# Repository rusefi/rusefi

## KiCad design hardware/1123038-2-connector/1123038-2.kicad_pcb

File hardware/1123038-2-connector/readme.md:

72 pin connector Mazda Miata MX-5 NB2

# [For sale here](https://www.tindie.com/products/russian/72p-connector-bare-pcb-miata-nb2/)

[Known Issues](known_issues.txt)

[Forum thread](https://rusefi.com/forum/viewtopic.php?f=4&t=687)

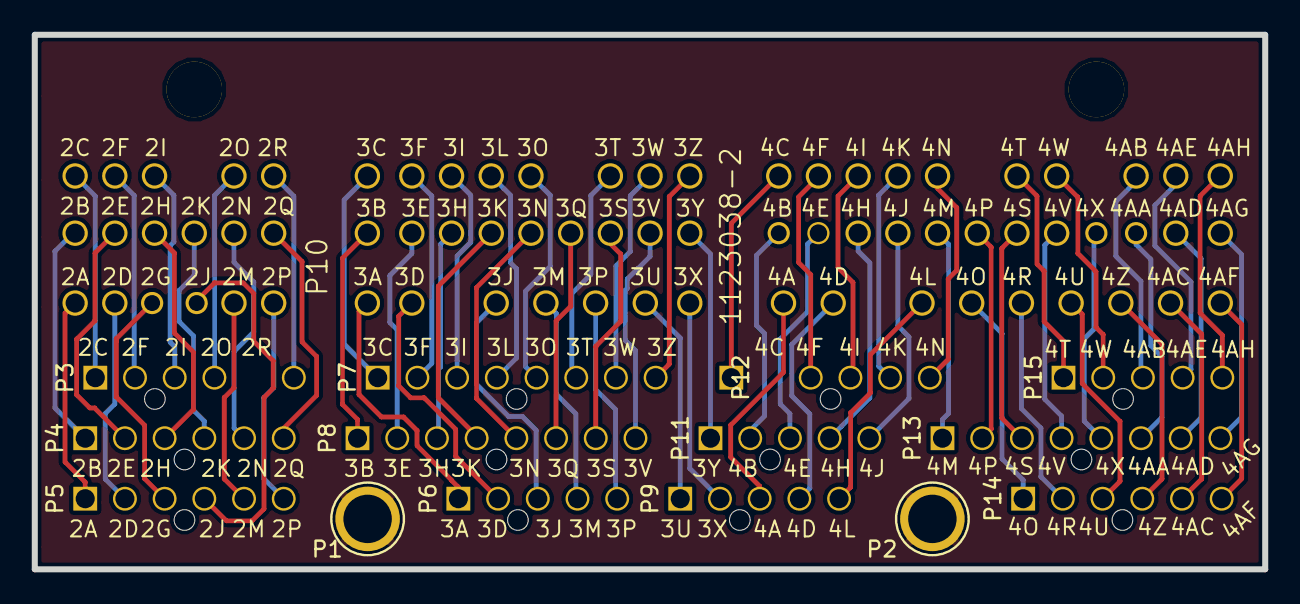
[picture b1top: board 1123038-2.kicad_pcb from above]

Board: 2 copper layers, 77.5 x 33.7 mm, 16 parts (1 on the bottom side), 73 nets.

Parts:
G1: LOGO
P1, P2: CONN_1; 1pin
P3, P6, P9, P11, P12, P15: CONN_01X05; Molex_NanoFit_1x05x2.50mm_Straight
P4, P5, P14: CONN_01X06; Molex_NanoFit_1x06x2.50mm_Straight
P7, P8, P13: CONN_01X08; Molex_NanoFit_1x08x2.50mm_Straight
P10: 1123038-2

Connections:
/2A: P5.1, P10.51
/2B: P4.1, P10.24
/2C: P3.1, P10.1
/2D: P5.2, P10.52
/2E: P4.2, P10.25
/2F: P3.2, P10.2
/2G: P5.3, P10.53
/2H: P4.3, P10.26
/2I: P3.3, P10.3
/2J: P5.4, P10.54
/2K: P4.4, P10.27
/2M: P5.5, P10.55
/2N: P4.5, P10.28
/2P: P5.6, P10.56
/2Q: P4.6, P10.29
/2R: P3.5, P10.5
/3A: P6.1, P10.57
/3B: P8.1, P10.30
/3C: P7.1, P10.6
/3D: P6.2, P10.58
/3E: P8.2, P10.31
/3F: P7.2, P10.7
/3H: P8.3, P10.32
/3I: P7.3, P10.8
/3J: P6.3, P10.59
/3K: P8.4, P10.33
/3L: P7.4, P10.9
/3M: P6.4, P10.60
/3N: P8.5, P10.34
/3O: P7.5, P10.10
/3P: P6.5, P10.61
/3Q: P8.6, P10.35
/3S: P8.7, P10.36
/3T: P7.6, P10.11
/3U: P9.1, P10.62
/3V: P8.8, P10.37
/3W: P7.7, P10.12
/3X: P9.2, P10.63
/3Y: P10.38, P11.1
/3Z: P7.8, P10.13
/4A: P9.3, P10.64
/4AA: P10.48, P13.6
/4AB: P10.21, P15.3
/4AC: P10.71, P14.5
/4AD: P10.49, P13.7
/4AE: P10.22, P15.4
/4AF: P10.72, P14.6
/4AG: P10.50, P13.8
/4AH: P10.23, P15.5
/4B: P10.39, P11.2
/4C: P10.14, P12.1
/4D: P9.4, P10.65
/4E: P10.40, P11.3
/4F: P10.15, P12.2
/4H: P10.41, P11.4
/4I: P10.16, P12.3
/4J: P10.42, P11.5
/4K: P10.17, P12.4
/4L: P9.5, P10.66
/4M: P10.43, P13.1
/4N: P10.18, P12.5
/4O: P10.67, P14.1
/4P: P10.44, P13.2
/4R: P10.68, P14.2
/4S: P10.45, P13.3
/4T: P10.19, P15.1
/4U: P10.69, P14.3
/4V: P10.46, P13.4
/4W: P10.20, P15.2
/4X: P10.47, P13.5
/4Z: P10.70, P14.4
/20: P3.4, P10.4
GND: P1.1, P2.1

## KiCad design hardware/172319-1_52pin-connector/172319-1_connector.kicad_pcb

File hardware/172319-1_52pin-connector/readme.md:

52 pin connector Mitsubishi Galant VR4 Eclipse 1G

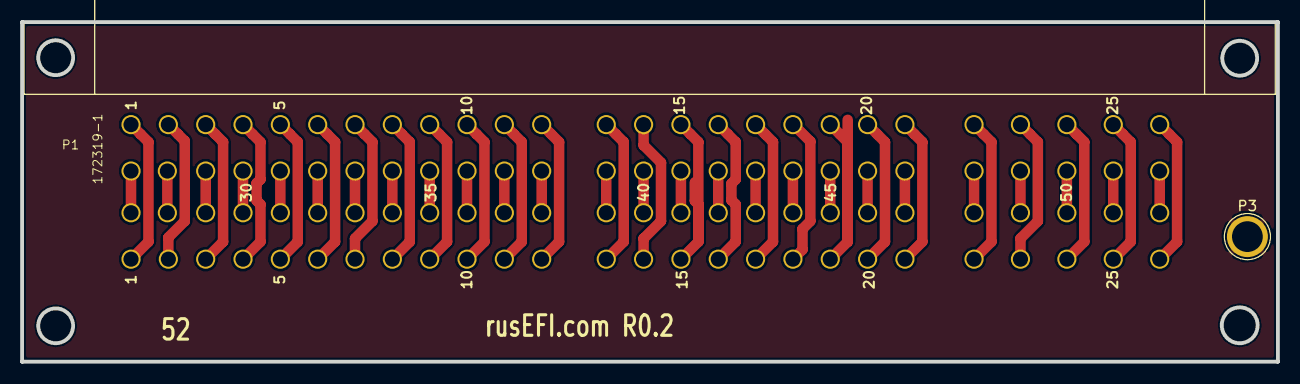
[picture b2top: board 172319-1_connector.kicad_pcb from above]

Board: 2 copper layers, 124.5 x 33.7 mm, 3 parts (1 on the bottom side), 52 nets.

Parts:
P1, P2: 172319-1; 172319-1_connector
P3: CONN_01X01; 1pin

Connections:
unnamed: P1.1, P2.1
unnamed: P1.2, P2.2
unnamed: P1.3, P2.3
unnamed: P1.4, P2.4
unnamed: P1.5, P2.5
unnamed: P1.6, P2.6
unnamed: P1.7, P2.7
unnamed: P1.8, P2.8
unnamed: P1.9, P2.9
unnamed: P1.10, P2.10
unnamed: P1.11, P2.11
unnamed: P1.12, P2.12
unnamed: P1.13, P2.13
unnamed: P1.14, P2.14
unnamed: P1.15, P2.15
unnamed: P1.16, P2.16
unnamed: P1.17, P2.17
unnamed: P1.18, P2.18
unnamed: P1.19, P2.19
unnamed: P1.20, P2.20
unnamed: P1.21, P2.21
unnamed: P1.22, P2.22
unnamed: P1.23, P2.23
unnamed: P1.24, P2.24
unnamed: P1.25, P2.25
unnamed: P1.26, P2.26
unnamed: P1.27, P2.27
unnamed: P1.28, P2.28
unnamed: P1.29, P2.29
unnamed: P1.30, P2.30
unnamed: P1.31, P2.31
unnamed: P1.32, P2.32
unnamed: P1.33, P2.33
unnamed: P1.34, P2.34
unnamed: P1.35, P2.35
unnamed: P1.36, P2.36
unnamed: P1.37, P2.37
unnamed: P1.38, P2.38
unnamed: P1.39, P2.39
unnamed: P1.40, P2.40
unnamed: P1.41, P2.41
unnamed: P1.42, P2.42
unnamed: P1.43, P2.43
unnamed: P1.44, P2.44
unnamed: P1.45, P2.45
unnamed: P1.46, P2.46
unnamed: P1.47, P2.47
unnamed: P1.48, P2.48
unnamed: P1.49, P2.49
unnamed: P1.50, P2.50
unnamed: P1.51, P2.51
unnamed: P1.52, P2.52

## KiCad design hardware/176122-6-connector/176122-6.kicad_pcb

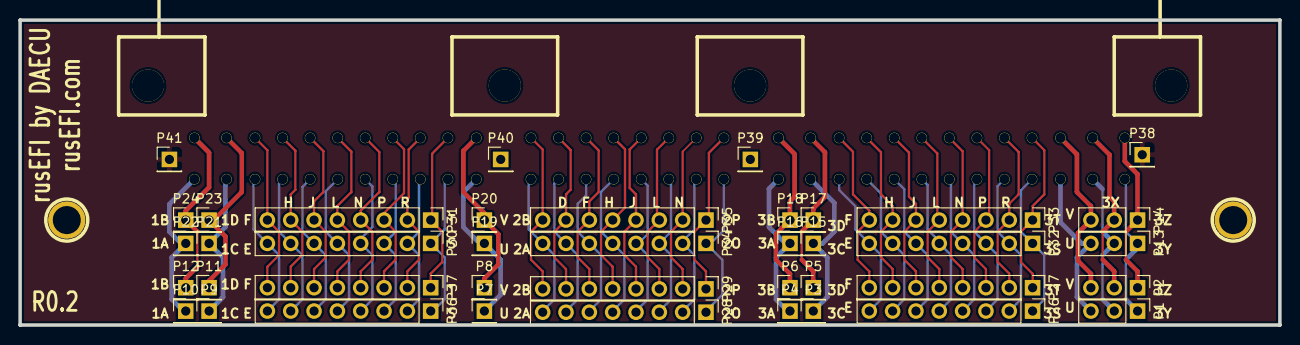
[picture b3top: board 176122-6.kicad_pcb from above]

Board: 2 copper layers, 137.2 x 33.2 mm, 43 parts (0 on the bottom side), 65 nets.

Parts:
1PIN, 1PIN#2: P***; 1pin
P1, P2, P13, P14: CONN_3; PinHeader_1x03_P2.54mm_Vertical
P3, P4, P5, P6, P7, P8, P9, P10, P11, P12, P15, P16, P17, P18, P19, P20, P21, P22, P23, P24, P38, P39, P40, P41: CONN_1; PinHeader_1x01_P2.54mm_Vertical
P25: 0176122-06; 176122-6
P26, P27, P28, P29, P30, P31, P32, P33, P34, P35, P36, P37: CONN_8; PinHeader_1x08_P2.54mm_Vertical

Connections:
GND: P38.1, P41.1
unnamed: P1.1, P13.1, P25.1
unnamed: P1.2, P13.2, P25.2
unnamed: P1.3, P13.3, P25.3
unnamed: P10.1, P22.1, P25.14
unnamed: P11.1, P23.1, P25.15
unnamed: P12.1, P24.1, P25.16
unnamed: P2.1, P14.1, P25.4
unnamed: P2.2, P14.2, P25.5
unnamed: P2.3, P14.3, P25.6
unnamed: P3.1, P15.1, P25.7
unnamed: P4.1, P16.1, P25.8
unnamed: P5.1, P17.1, P25.9
unnamed: P6.1, P18.1, P25.10
unnamed: P7.1, P19.1, P25.11
unnamed: P8.1, P20.1, P25.12
unnamed: P9.1, P21.1, P25.13
unnamed: P25.17, P26.1, P32.1
unnamed: P25.18, P26.2, P32.2
unnamed: P25.19, P26.3, P32.3
unnamed: P25.20, P26.4, P32.4
unnamed: P25.21, P26.5, P32.5
unnamed: P25.22, P26.6, P32.6
unnamed: P25.23, P26.7, P32.7
unnamed: P25.24, P26.8, P32.8
unnamed: P25.25, P27.1, P33.1
unnamed: P25.26, P27.2, P33.2
unnamed: P25.27, P27.3, P33.3
unnamed: P25.28, P27.4, P33.4
unnamed: P25.29, P27.5, P33.5
unnamed: P25.30, P27.6, P33.6
unnamed: P25.31, P27.7, P33.7
unnamed: P25.32, P27.8, P33.8
unnamed: P25.33, P28.1, P34.1
unnamed: P25.34, P28.2, P34.2
unnamed: P25.35, P28.3, P34.3
unnamed: P25.36, P28.4, P34.4
unnamed: P25.37, P28.5, P34.5
unnamed: P25.38, P28.6, P34.6
unnamed: P25.39, P28.7, P34.7
unnamed: P25.40, P28.8, P34.8
unnamed: P25.41, P29.1, P35.1
unnamed: P25.42, P29.2, P35.2
unnamed: P25.43, P29.3, P35.3
unnamed: P25.44, P29.4, P35.4
unnamed: P25.45, P29.5, P35.5
unnamed: P25.46, P29.6, P35.6
unnamed: P25.47, P29.7, P35.7
unnamed: P25.48, P29.8, P35.8
unnamed: P25.49, P30.1, P36.1
unnamed: P25.50, P30.2, P36.2
unnamed: P25.51, P30.3, P36.3
unnamed: P25.52, P30.4, P36.4
unnamed: P25.53, P30.5, P36.5
unnamed: P25.54, P30.6, P36.6
unnamed: P25.55, P30.7, P36.7
unnamed: P25.56, P30.8, P36.8
unnamed: P25.57, P31.1, P37.1
unnamed: P25.58, P31.2, P37.2
unnamed: P25.59, P31.3, P37.3
unnamed: P25.60, P31.4, P37.4
unnamed: P25.61, P31.5, P37.5
unnamed: P25.62, P31.6, P37.6
unnamed: P25.63, P31.7, P37.7
unnamed: P25.64, P31.8, P37.8

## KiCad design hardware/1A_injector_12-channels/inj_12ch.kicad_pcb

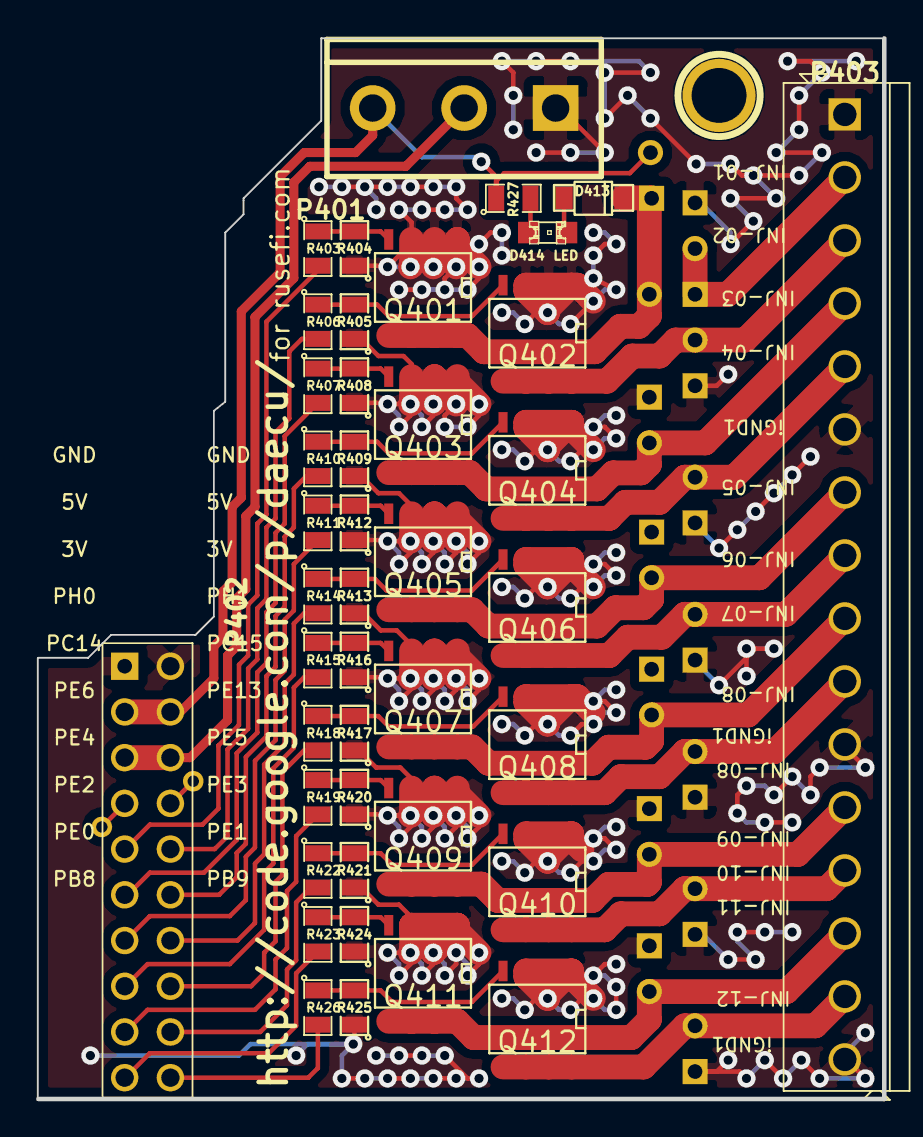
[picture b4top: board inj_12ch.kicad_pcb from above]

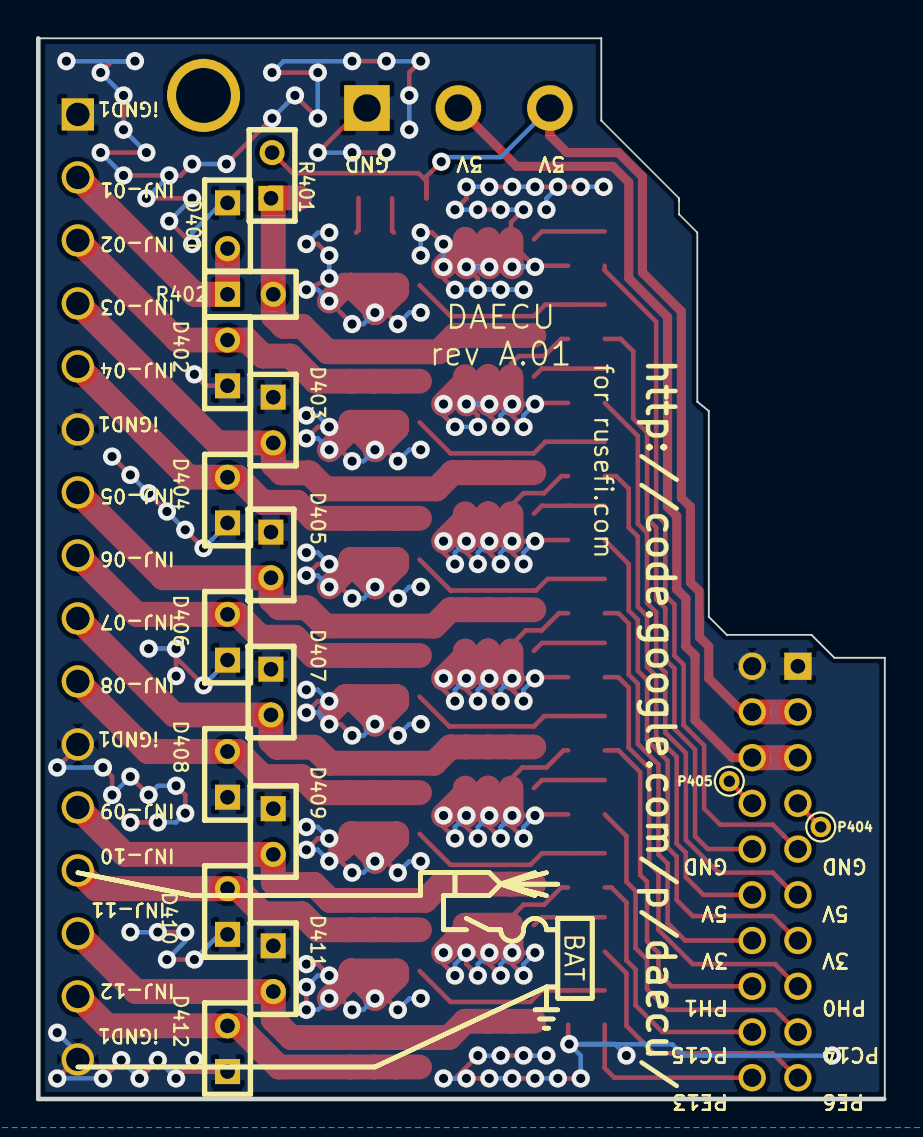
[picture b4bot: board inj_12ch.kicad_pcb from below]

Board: 2 copper layers, 47.0 x 58.9 mm, 59 parts (16 on the bottom side), 44 nets.

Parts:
D401, D402, D403, D404, D405, D406, D407, D408, D409, D410, D411, D412: DIODE; SIL-2
D413: DIODE; SOD-123
D414: LED; LED-0805
M401: CONN_1; 1pin
P401: CONN_3; bornier3
P402: CONN_10X2; pin_array_10x2
P403: CONN_16; SIL-16_3.5MM
P404, P405: CONN_1; PINTST
Q401, Q402, Q403, Q404, Q405, Q406, Q407, Q408, Q409, Q410, Q411, Q412: OVP_DRIVER; SO8E_ST
R401: OPT; SIL-2
R402: 0R; SIL-2
R403, R406, R407, R410, R411, R414, R415, R418, R419, R422, R423, R426: 20R; SM0805
R404, R405, R408, R409, R412, R413, R416, R417, R420, R421, R424, R425, R427: 1K; SM0805

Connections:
/3.3V: P401.2, P402.5, P402.6
/5V: P401.3, P402.3, P402.4, R401.2, R427.1
/INJ-01: D413.2, Q401.2, R401.1, R402.2
/INJ-01_2: D401.2, P403.2, R402.1
/INJ-01_5V: P402.9, R403.2
/INJ-02: D402.2, P403.3, Q402.2
/INJ-02_5V: P402.10, R406.2
/INJ-03: D403.2, P403.4, Q403.2
/INJ-03_5V: P402.11, R407.2
/INJ-04: D404.2, P403.5, Q404.2
/INJ-04_5V: P402.12, R410.2
/INJ-05: D405.2, P403.7, Q405.2
/INJ-05_5V: P402.13, R411.2
/INJ-06: D406.2, P403.8, Q406.2
/INJ-06_5V: P402.14, R414.2
/INJ-07: D407.2, P403.9, Q407.2
/INJ-07_5V: P402.15, R415.2
/INJ-08: D408.2, P403.10, Q408.2
/INJ-08_5V: P402.16, R418.2
/INJ-09: D409.2, P403.12, Q409.2
/INJ-09_5V: P402.17, R419.2
/INJ-10: D410.2, P403.13, Q410.2
/INJ-10_5V: P402.18, R422.2
/INJ-11: D411.2, P403.14, Q411.2
/INJ-11_5V: P402.19, R423.2
/INJ-12: D412.2, P403.15, Q412.2
/INJ-12_5V: P402.20, R426.2
/PH0: P402.7, P404.1
/PH1: P402.8, P405.1
GND: D401.1, D402.1, D403.1, D404.1, D405.1, D406.1, D407.1, D408.1, D409.1, D410.1, D411.1, D412.1, P401.1, P402.1, P402.2, P403.1, P403.6, P403.11, P403.16, Q401.3, Q402.3, Q403.3, Q404.3, Q405.3, Q406.3, Q407.3, Q408.3, Q409.3, Q410.3, Q411.3, Q412.3, R404.1, R405.1, R408.1, R409.1, R412.1, R413.1, R416.1, R417.1, R420.1, R421.1, R424.1, R425.1
unnamed: Q408.1, R417.2, R418.1
unnamed: Q410.1, R421.2, R422.1
unnamed: Q412.1, R425.2, R426.1
unnamed: Q404.1, R409.2, R410.1
unnamed: Q406.1, R413.2, R414.1
unnamed: Q402.1, R405.2, R406.1
unnamed: D414.1, R427.2
unnamed: D413.1, D414.2
unnamed: Q401.1, R403.1, R404.2
unnamed: Q405.1, R411.1, R412.2
unnamed: Q403.1, R407.1, R408.2
unnamed: Q409.1, R419.1, R420.2
unnamed: Q407.1, R415.1, R416.2
unnamed: Q411.1, R423.1, R424.2

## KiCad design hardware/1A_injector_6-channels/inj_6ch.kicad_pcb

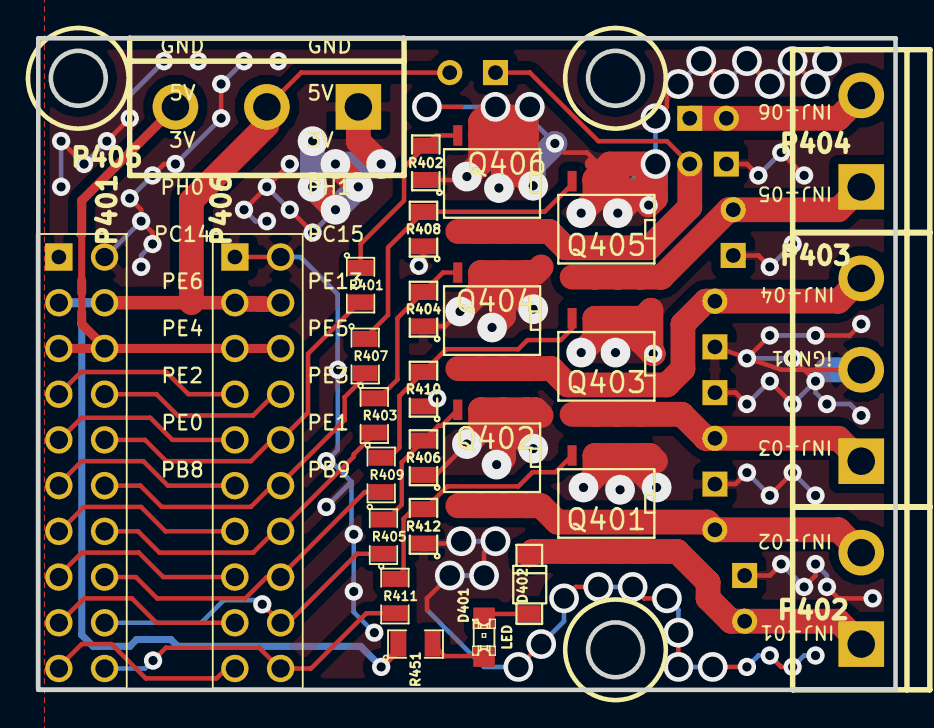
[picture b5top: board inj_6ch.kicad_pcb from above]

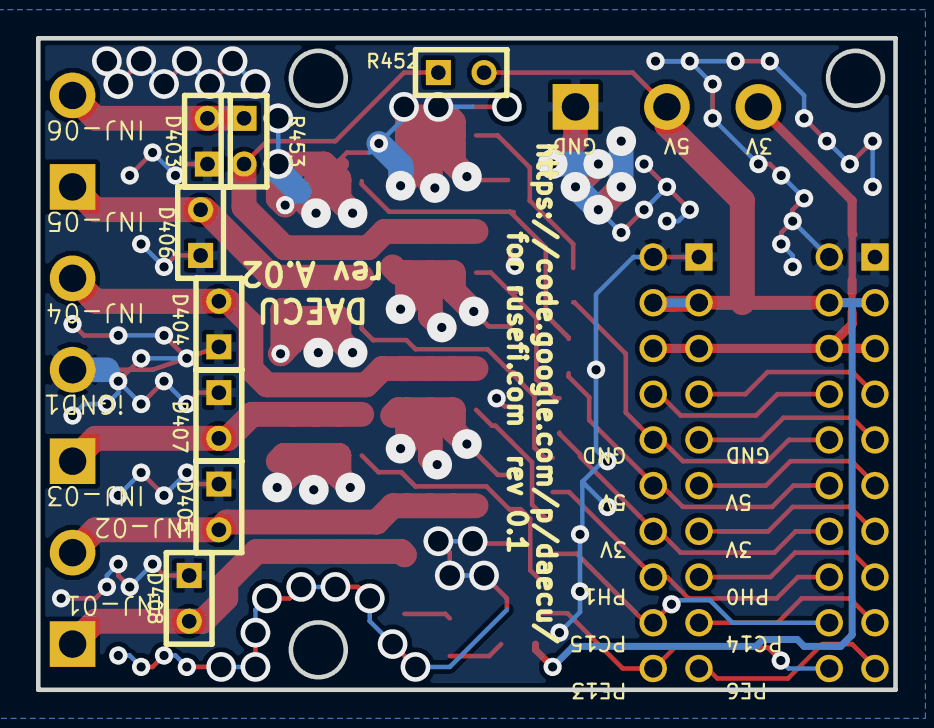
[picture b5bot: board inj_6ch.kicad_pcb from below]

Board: 2 copper layers, 47.6 x 36.2 mm, 35 parts (8 on the bottom side), 32 nets.

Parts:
D401: LED; LED-0805
D402: DIODE; SOD-123
D403, D404, D405, D406, D407, D408: DIODE; SIL-2
P401, P406: HEADER_10X2; pin_array_10x2
P402, P404: CONN_2; bornier2
P403, P405: CONN_3; bornier3
Q401, Q402, Q403, Q404, Q405, Q406: OVP_DRIVER; SO8E_ST
R401, R403, R405, R407, R409, R411: 20R; SM0805
R402, R404, R406, R408, R410, R412, R451: 1K; SM0805
R452: OPT; SIL-2
R453: 0R; SIL-2

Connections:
/3.3V: P401.5, P401.6, P405.3, P406.5, P406.6
/5V: P401.3, P401.4, P405.2, P406.3, P406.4, R451.1, R452.2
/INJ-01: D402.2, D408.2, P402.1, Q401.2
/INJ-01_5V: P401.20, P406.20, R411.2
/INJ-02: D405.2, P402.2, Q402.2
/INJ-02_5V: P401.18, P406.18, R405.2
/INJ-03: D407.2, P403.1, Q403.2
/INJ-03_5V: P401.16, P406.16, R409.2
/INJ-04: D404.2, P403.3, Q404.2
/INJ-04_5V: P401.14, P406.14, R403.2
/INJ-05: D406.2, P404.1, Q405.2
/INJ-05_5V: P401.12, P406.12, R407.2
/INJ-06: Q406.2, R452.1, R453.2
/INJ-06_2: D403.2, P404.2, R453.1
/INJ-06_5V: P401.10, P406.10, R401.2
/PB8: P401.19, P406.19
/PC14: P401.9, P406.9
/PE0: P401.17, P406.17
/PE2: P401.15, P406.15
/PE4: P401.13, P406.13
/PE6: P401.11, P406.11
/PH0: P401.7, P406.7
/PH1: P401.8, P406.8
GND: D403.1, D404.1, D405.1, D406.1, D407.1, D408.1, P401.1, P401.2, P403.2, P405.1, P406.1, P406.2, Q401.3, Q402.3, Q403.3, Q404.3, Q405.3, Q406.3, R402.1, R404.1, R406.1, R408.1, R410.1, R412.1
unnamed: D401.1, R451.2
unnamed: D401.2, D402.1
unnamed: Q406.1, R401.1, R402.2
unnamed: Q404.1, R403.1, R404.2
unnamed: Q403.1, R409.1, R410.2
unnamed: Q402.1, R405.1, R406.2
unnamed: Q401.1, R411.1, R412.2
unnamed: Q405.1, R407.1, R408.2

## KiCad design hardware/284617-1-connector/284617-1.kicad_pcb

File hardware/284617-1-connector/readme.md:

154 pin Audi Volkswagen ECU connector

# [Connector for sale here](https://www.tindie.com/products/russian/154-pin-ecu-connector/)

https://rusefi.com/forum/viewtopic.php?f=4&t=582

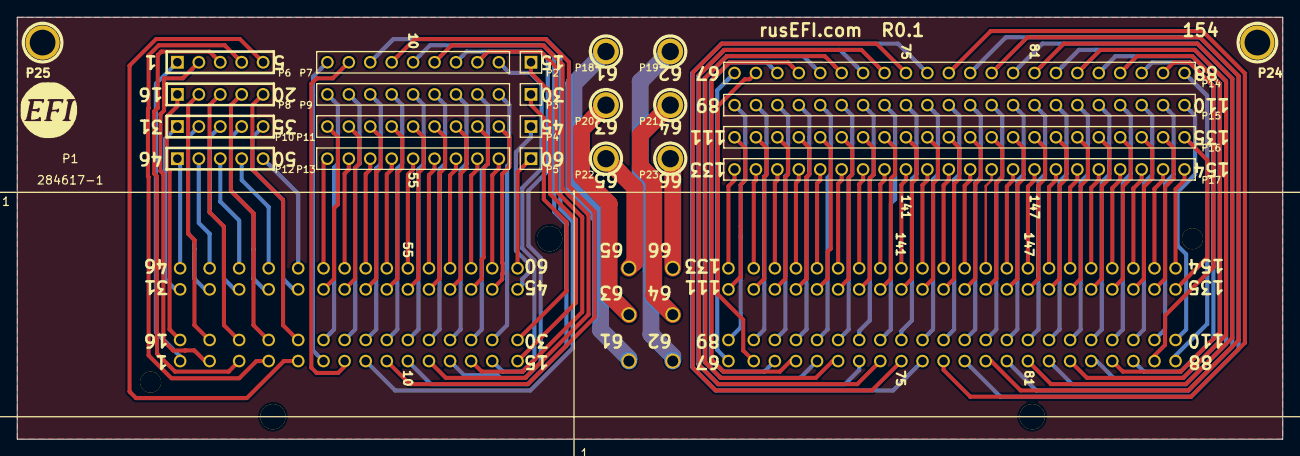
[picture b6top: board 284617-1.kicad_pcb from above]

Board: 2 copper layers, 150.0 x 50.0 mm, 27 parts (1 on the bottom side), 155 nets.

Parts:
G?: LOGO
G?#2: LOGO; LOGO_F
P1: 284617-1
P2, P3, P4, P5: CONN_1; PIN_ARRAY_1
P6, P8, P10, P12: CONN_5; PIN_ARRAY_5x1
P7, P9, P11, P13: CONN_9; PIN_ARRAY_9x1
P14, P15, P16, P17: CONN_22; PIN_ARRAY_22x1
P18, P19, P20, P21, P22, P23: CONN_1; 1pin(m)
P24, P25: CONN_1; 1pin

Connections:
/GND: P24.1, P25.1
unnamed: P1.94, P15.6
unnamed: P1.108, P15.20
unnamed: P1.107, P15.19
unnamed: P1.106, P15.18
unnamed: P1.105, P15.17
unnamed: P1.104, P15.16
unnamed: P1.103, P15.15
unnamed: P1.102, P15.14
unnamed: P1.101, P15.13
unnamed: P1.100, P15.12
unnamed: P1.99, P15.11
unnamed: P1.98, P15.10
unnamed: P1.97, P15.9
unnamed: P1.96, P15.8
unnamed: P1.95, P15.7
unnamed: P1.109, P15.21
unnamed: P1.93, P15.5
unnamed: P1.92, P15.4
unnamed: P1.91, P15.3
unnamed: P1.90, P15.2
unnamed: P1.89, P15.1
unnamed: P1.88, P14.22
unnamed: P1.87, P14.21
unnamed: P1.86, P14.20
unnamed: P1.85, P14.19
unnamed: P1.84, P14.18
unnamed: P1.83, P14.17
unnamed: P1.82, P14.16
unnamed: P1.81, P14.15
unnamed: P1.80, P14.14
unnamed: P1.123, P16.13
unnamed: P1.137, P17.5
unnamed: P1.136, P17.4
unnamed: P1.135, P17.3
unnamed: P1.134, P17.2
unnamed: P1.133, P17.1
unnamed: P1.132, P16.22
unnamed: P1.131, P16.21
unnamed: P1.130, P16.20
unnamed: P1.129, P16.19
unnamed: P1.128, P16.18
unnamed: P1.127, P16.17
unnamed: P1.126, P16.16
unnamed: P1.125, P16.15
unnamed: P1.124, P16.14
unnamed: P1.79, P14.13
unnamed: P1.122, P16.12
unnamed: P1.121, P16.11
unnamed: P1.120, P16.10
unnamed: P1.119, P16.9
unnamed: P1.118, P16.8
unnamed: P1.117, P16.7
unnamed: P1.116, P16.6
unnamed: P1.115, P16.5
unnamed: P1.114, P16.4
unnamed: P1.113, P16.3
unnamed: P1.112, P16.2
unnamed: P1.111, P16.1
unnamed: P1.110, P15.22
unnamed: P1.138, P17.6
unnamed: P1.78, P14.12
unnamed: P1.77, P14.11
unnamed: P1.76, P14.10
unnamed: P1.75, P14.9
unnamed: P1.74, P14.8
unnamed: P1.73, P14.7
unnamed: P1.72, P14.6
unnamed: P1.71, P14.5
unnamed: P1.70, P14.4
unnamed: P1.69, P14.3
unnamed: P1.68, P14.2
unnamed: P1.67, P14.1
unnamed: P1.154, P17.22
unnamed: P1.144, P17.12
unnamed: P1.153, P17.21
unnamed: P1.143, P17.11
unnamed: P1.152, P17.20
unnamed: P1.142, P17.10
unnamed: P1.151, P17.19
unnamed: P1.141, P17.9
unnamed: P1.150, P17.18
unnamed: P1.140, P17.8
unnamed: P1.147, P17.15
unnamed: P1.149, P17.17
unnamed: P1.139, P17.7
unnamed: P1.148, P17.16
unnamed: P1.146, P17.14
unnamed: P1.145, P17.13
unnamed: P1.62, P19.1
unnamed: P1.61, P18.1
unnamed: P1.45, P4.1
unnamed: P1.63, P20.1
unnamed: P1.66, P23.1
unnamed: P1.65, P22.1
unnamed: P1.64, P21.1
unnamed: P1.1, P6.1
unnamed: P1.59, P13.9
unnamed: P1.49, P12.4
unnamed: P1.60, P5.1
unnamed: P1.43, P11.8
unnamed: P1.33, P10.3
unnamed: P1.23, P9.3
unnamed: P1.13, P7.8
unnamed: P1.52, P13.2
unnamed: P1.42, P11.7
unnamed: P1.32, P10.2
unnamed: P1.22, P9.2
unnamed: P1.12, P7.7
unnamed: P1.51, P13.1
unnamed: P1.41, P11.6
unnamed: P1.31, P10.1
unnamed: P1.21, P9.1
unnamed: P1.11, P7.6
unnamed: P1.53, P13.3
unnamed: P1.50, P12.5
unnamed: P1.40, P11.5
unnamed: P1.30, P3.1
unnamed: P1.20, P8.5
unnamed: P1.10, P7.5
unnamed: P1.9, P7.4
unnamed: P1.8, P7.3
unnamed: P1.7, P7.2
unnamed: P1.6, P7.1
unnamed: P1.5, P6.5
unnamed: P1.4, P6.4
unnamed: P1.3, P6.3
unnamed: P1.2, P6.2
unnamed: P1.46, P12.1
unnamed: P1.39, P11.4
unnamed: P1.29, P9.9
unnamed: P1.19, P8.4
unnamed: P1.48, P12.3
unnamed: P1.38, P11.3
unnamed: P1.28, P9.8
unnamed: P1.18, P8.3
unnamed: P1.57, P13.7
unnamed: P1.47, P12.2
unnamed: P1.37, P11.2
unnamed: P1.27, P9.7
unnamed: P1.17, P8.2
unnamed: P1.56, P13.6
unnamed: P1.58, P13.8
unnamed: P1.36, P11.1
unnamed: P1.26, P9.6
unnamed: P1.16, P8.1
unnamed: P1.55, P13.5
unnamed: P1.35, P10.5
unnamed: P1.25, P9.5
unnamed: P1.15, P2.1
unnamed: P1.54, P13.4
unnamed: P1.44, P11.9
unnamed: P1.34, P10.4
unnamed: P1.24, P9.4
unnamed: P1.14, P7.9

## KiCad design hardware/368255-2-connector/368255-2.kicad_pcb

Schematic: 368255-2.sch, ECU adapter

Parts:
P1: 368255-2; MODULE
P2, P3, P4, P5: CONN_19
P6, P7, P8, P9, P10, P11, P12, P13, P14, P15, P16, P17, P18, P19, P20, P21, P22, P23, P24, P25, P26, P27, P28, P29, P30, P31, P36, P37: CONN_1
P32, P33, P34, P35: CONN_8

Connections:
GND: P36.1, P37.1
unnamed: P1.22, P2.17
unnamed: P1.34, P3.10
unnamed: P1.33, P3.9
unnamed: P1.32, P3.8
unnamed: P1.31, P3.7
unnamed: P1.30, P3.6
unnamed: P1.29, P3.5
unnamed: P1.28, P3.4
unnamed: P1.27, P3.3
unnamed: P1.26, P3.2
unnamed: P1.25, P3.1
unnamed: P1.24, P2.19
unnamed: P1.23, P2.18
unnamed: P1.35, P3.11
unnamed: P1.21, P2.16
unnamed: P1.20, P2.15
unnamed: P1.19, P2.14
unnamed: P1.18, P2.13
unnamed: P1.17, P2.12
unnamed: P1.16, P2.11
unnamed: P1.15, P2.10
unnamed: P1.14, P2.9
unnamed: P1.13, P2.8
unnamed: P1.12, P2.7
unnamed: P1.11, P2.6
unnamed: P1.10, P2.5
unnamed: P1.48, P4.5
unnamed: P1.60, P4.17
unnamed: P1.59, P4.16
unnamed: P1.58, P4.15
unnamed: P1.57, P4.14
unnamed: P1.56, P4.13
unnamed: P1.55, P4.12
unnamed: P1.54, P4.11
unnamed: P1.53, P4.10
unnamed: P1.52, P4.9
unnamed: P1.51, P4.8
unnamed: P1.50, P4.7
unnamed: P1.49, P4.6
unnamed: P1.9, P2.4
unnamed: P1.47, P4.4
unnamed: P1.46, P4.3
unnamed: P1.45, P4.2
unnamed: P1.44, P4.1
unnamed: P1.43, P3.19
unnamed: P1.42, P3.18
unnamed: P1.41, P3.17
unnamed: P1.40, P3.16
unnamed: P1.39, P3.15
unnamed: P1.38, P3.14
unnamed: P1.37, P3.13
unnamed: P1.36, P3.12
unnamed: P1.94, P33.5
unnamed: P1.106, P35.1
unnamed: P1.105, P34.8
unnamed: P1.104, P34.7
unnamed: P1.103, P34.6
unnamed: P1.102, P34.5
unnamed: P1.101, P34.4
unnamed: P1.100, P34.3
unnamed: P1.99, P34.2
unnamed: P1.98, P34.1
unnamed: P1.97, P33.8
unnamed: P1.96, P33.7
unnamed: P1.95, P33.6
unnamed: P1.107, P35.2
unnamed: P1.93, P33.4
unnamed: P1.92, P33.3
unnamed: P1.91, P33.2
unnamed: P1.90, P33.1
unnamed: P1.89, P32.8
unnamed: P1.88, P32.7
unnamed: P1.87, P32.6
unnamed: P1.86, P32.5
unnamed: P1.85, P32.4
unnamed: P1.84, P32.3
unnamed: P1.83, P32.2
unnamed: P1.82, P32.1
unnamed: P1.117, P24.1, P25.1
unnamed: P1.8, P2.3
unnamed: P1.7, P2.2
unnamed: P1.6, P2.1
unnamed: P1.120, P18.1, P19.1
unnamed: P1.118, P22.1, P23.1
unnamed: P1.61, P4.18
unnamed: P1.116, P26.1, P27.1
unnamed: P1.115, P28.1, P29.1
unnamed: P1.114, P30.1, P31.1
unnamed: P1.113, P35.8
unnamed: P1.112, P35.7
unnamed: P1.111, P35.6
unnamed: P1.110, P35.5
unnamed: P1.109, P35.4
unnamed: P1.108, P35.3
unnamed: P1.121, P16.1, P17.1
unnamed: P1.119, P20.1, P21.1
unnamed: P1.74, P5.12
unnamed: P1.81, P5.19
unnamed: P1.80, P5.18
unnamed: P1.79, P5.17
unnamed: P1.78, P5.16
unnamed: P1.77, P5.15
unnamed: P1.76, P5.14
unnamed: P1.75, P5.13
unnamed: P1.73, P5.11
unnamed: P1.72, P5.10
unnamed: P1.71, P5.9
unnamed: P1.70, P5.8
unnamed: P1.69, P5.7
unnamed: P1.68, P5.6
unnamed: P1.67, P5.5
unnamed: P1.66, P5.4
unnamed: P1.65, P5.3
unnamed: P1.64, P5.2
unnamed: P1.63, P5.1
unnamed: P1.62, P4.19
unnamed: P1.5, P6.1, P7.1
unnamed: P1.4, P8.1, P9.1
unnamed: P1.3, P10.1, P11.1
unnamed: P1.2, P12.1, P13.1
unnamed: P1.1, P14.1, P15.1

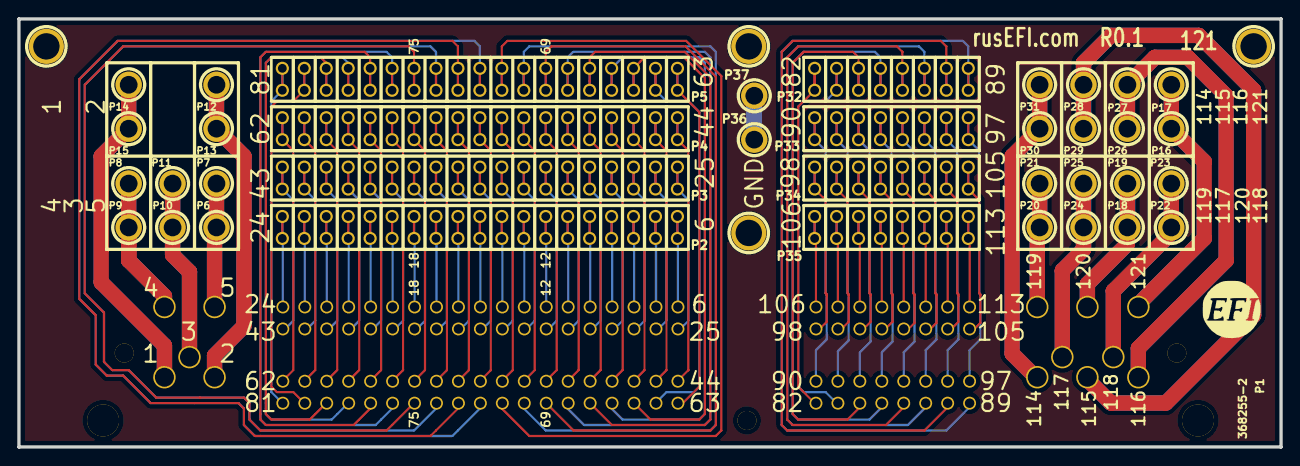
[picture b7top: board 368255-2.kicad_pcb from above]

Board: 2 copper layers, 146.1 x 49.5 mm, 43 parts (1 on the bottom side), 122 nets.

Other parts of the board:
1PIN, 1PIN#2, 1PIN#3, 1PIN#4: P***; 1pin
G?: LOGO
G?#2: LOGO; LOGO_F

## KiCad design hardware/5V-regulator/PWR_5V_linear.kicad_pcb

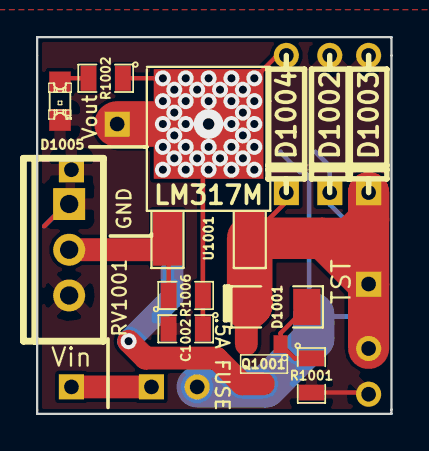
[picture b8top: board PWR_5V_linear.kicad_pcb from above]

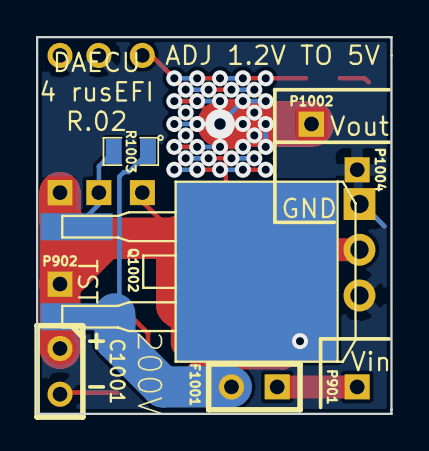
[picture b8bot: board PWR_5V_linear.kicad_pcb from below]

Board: 2 copper layers, 19.7 x 20.9 mm, 20 parts (8 on the bottom side), 10 nets.

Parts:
C1001: 0.1uF 50V; C1
C1002: 1uF 16V; SM0805
D1001: 7.5V; SM1206
D1002: 15V; D3
D1003, D1004: 24V; D3
D1005: LED-grn; LED-0805
F1001: 5A; SIL-2
P901, P902, P1002, P1004: CONN_1; SIL-1
Q1001: 30V; SOT23
Q1002: 200V; m-pad-2.1-TO-263AB
R1001, R1002: 1k; SM0805
R1003: 100k; SM0805
R1006: 240R; SM0805
RV1001: 1k; TO220_VERT
U1001: LM317M; DPAK2

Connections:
/5V-REG: C1002.1, D1004.1, P1002.1, R1002.1, R1006.2, U1001.2
/VBAT: C1001.1, D1001.2, D1003.2, D1004.2, P902.1, Q1001.2, U1001.3
/Vf: F1001.2, Q1002.3, R1003.1
/Vin: F1001.1, P901.1
/Vs1: D1002.2, Q1002.1, R1003.2
/Vs2: Q1001.3, Q1002.2
GND: C1001.2, C1002.2, D1002.1, D1003.1, D1005.2, P1004.1, R1001.2, RV1001.1, RV1001.2
unnamed: R1006.1, RV1001.3, U1001.1
unnamed: D1001.1, Q1001.1, R1001.1
unnamed: D1005.1, R1002.2
